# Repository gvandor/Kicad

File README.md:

# Kicad
Theese are my Kicad projects. This is only a hobby.
Projects:
Sidetone: a morse voice generator (for HAM)
Novice: only learning.
Labortap: a power supply for research works

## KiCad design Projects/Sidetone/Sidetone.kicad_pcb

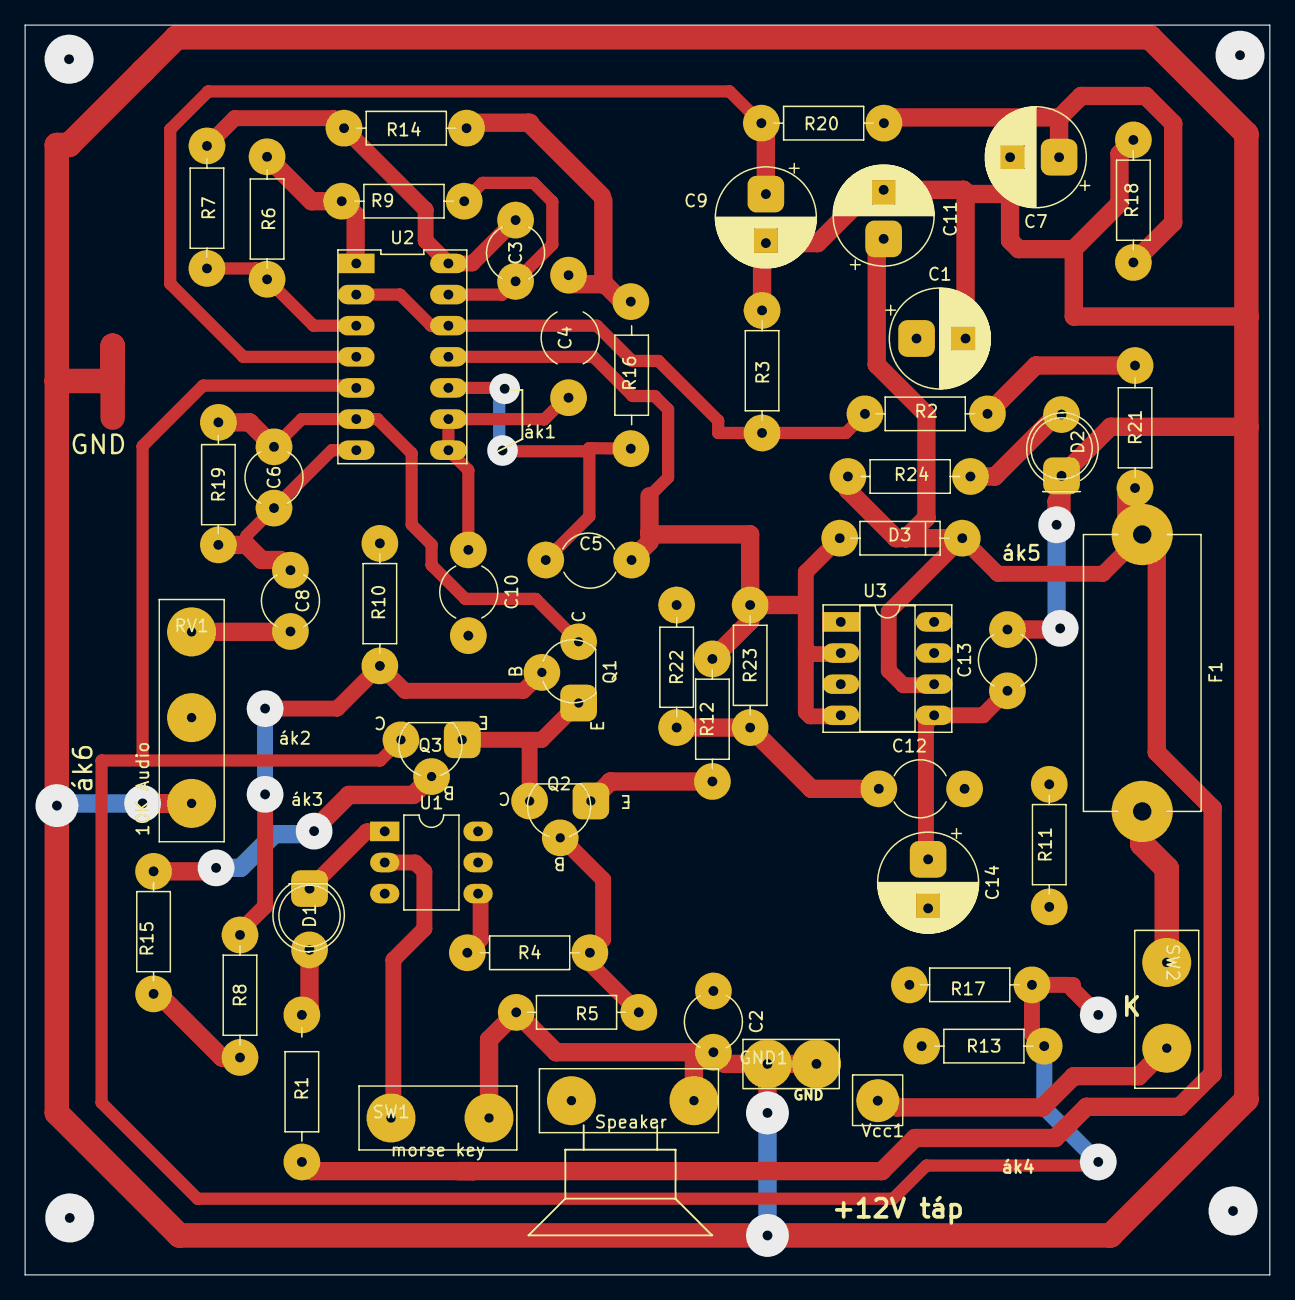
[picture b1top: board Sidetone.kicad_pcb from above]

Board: 2 copper layers, 101.6 x 102.0 mm, 54 parts (0 on the bottom side), 34 nets.

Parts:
4-8ohm1: Speaker; Hangszoro
C1, C7, C9, C11, C14: 100uF/16V; CP_Radial_Elektrolit_D8.0mm_P4.0mm_H12
C2, C4: 20nF; C_Radial_Ceramic_D4.5mm_P5.00mm
C3: 10 nF; C_Radial_Ceramic_D4.5mm_P5.00mm
C5, C6: 10nF; C_Radial_Ceramic_D4.5mm_P5.00mm
C8, C10, C12: 100nF; C_Radial_Ceramic_D4.5mm_P5.00mm
C13: 200nF; C_Radial_Ceramic_D4.5mm_P5.00mm
D1: Red; LED_D5.0mm_P5.0_Clear
D2: Power (Green); LED_D5.0mm_P5.0_Clear
D3: 1N4001; R_Axial_L6.3mm_D2.5mm_P10.0mm_Horizontal
F1: 1A; Fuseholder_22x10mm_Horizontal
GND1: GND
Q1, Q2, Q3: 2N3904; TO-92_Kis_Muanyag_Hazas_Transistor
R1: 750; R_Axial_L6.3mm_D2.5mm_P10.0mm_Horizontal
R2, R3: 10 K; R_Axial_L6.3mm_D2.5mm_P10.0mm_Horizontal
R4, R5: 220 K; R_Axial_L6.3mm_D2.5mm_P10.0mm_Horizontal
R6, R9: 100K; R_Axial_L6.3mm_D2.5mm_P10.0mm_Horizontal
R7: 47K; R_Axial_L6.3mm_D2.5mm_P10.0mm_Horizontal
R8, R15: 330; R_Axial_L6.3mm_D2.5mm_P10.0mm_Horizontal
R10, R17, R18, R19, R20: 10K; R_Axial_L6.3mm_D2.5mm_P10.0mm_Horizontal
R11, R12, R13: 22 K; R_Axial_L6.3mm_D2.5mm_P10.0mm_Horizontal
R14, R16: 33K; R_Axial_L6.3mm_D2.5mm_P10.0mm_Horizontal
R21: 10; R_Axial_L6.3mm_D2.5mm_P10.0mm_Horizontal
R22: 15K; R_Axial_L6.3mm_D2.5mm_P10.0mm_Horizontal
R23, R24: 1K; R_Axial_L6.3mm_D2.5mm_P10.0mm_Horizontal
RV1: 10K Audio; Potenciometer_4Pin_P7mm
SW1: morse key; Morse_Key_Pad_Group_2Pin_P7mm
SW2: On/off; Kapcsolo_Pad_Group_2Pin_P7mm
U1: 4N35; DIP-6_W7.62mm_LongPads
U2: LM324; DIP-14_LM324
U3: LM386; DIP-8_W7.62mm_Socket_LongPads
Vcc1: +Vcc

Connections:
GNDD: 4-8ohm1.2, C1.2, C2.2, C5.2, C7.2, C9.2, C11.2, C13.2, D2.1 (K), D3.2 (A), GND1.1, GND1.2, R3.2, R5.2, R12.2, R18.2, R23.2, RV1.3, SW1.2 (B), U2.11 (V-), U3.2 (-), U3.4 (GND)
unnamed: 4-8ohm1.1, C14.2
unnamed: C3.1, R7.1, R14.1, U2.14
unnamed: C4.2, R14.2, R16.1
unnamed: C7.1, R18.1, R20.2
unnamed: C8.2, RV1.1
unnamed: C10.2, R10.2
unnamed: C12.1, R22.2, R23.1
unnamed: C13.1, C14.1, U3.5
unnamed: D1.2 (A), R1.1
unnamed: D1.1 (K), U1.1
unnamed: D2.2 (A), R24.2
unnamed: C11.1, D3.1 (K), F1.1, R1.2, R21.2, R24.1, U3.6 (V+)
unnamed: Q1.2 (B), R8.2, R10.1
unnamed: C6.1, Q1.3 (C), R11.2, R19.1, U2.6 (-)
unnamed: Q1.1 (E), Q2.3 (C), Q3.1 (E)
unnamed: C2.1, Q2.2 (B), R4.2, R5.1
unnamed: Q2.1 (E), R12.1
unnamed: Q3.2 (B), R15.2
unnamed: Q3.3 (C), R13.2, R17.1, U2.5 (+)
unnamed: R4.1, U1.4
unnamed: R6.1, R9.1, U2.1
unnamed: R8.1, R15.1, R17.2
unnamed: R22.1, RV1.2
unnamed: SW1.1 (A), U1.2
unnamed: F1.2, SW2.1 (A)
unnamed: R6.2, R7.2, U2.3 (+)
unnamed: C1.1, R2.2, R3.1, U2.2 (-), U2.12 (+)
unnamed: C5.1, R16.2, U2.10 (+)
unnamed: C4.1, C10.1, U2.8, U2.9 (-)
unnamed: C3.2, R9.2, U2.13 (-)
unnamed: C6.2, C8.1, C9.1, R2.1, R11.1, R13.1, R19.2, R20.1, R21.1, U1.5, U2.4 (V+), U2.7
unnamed: C12.2, U3.3 (+)
VCC: SW2.2 (B), Vcc1.1

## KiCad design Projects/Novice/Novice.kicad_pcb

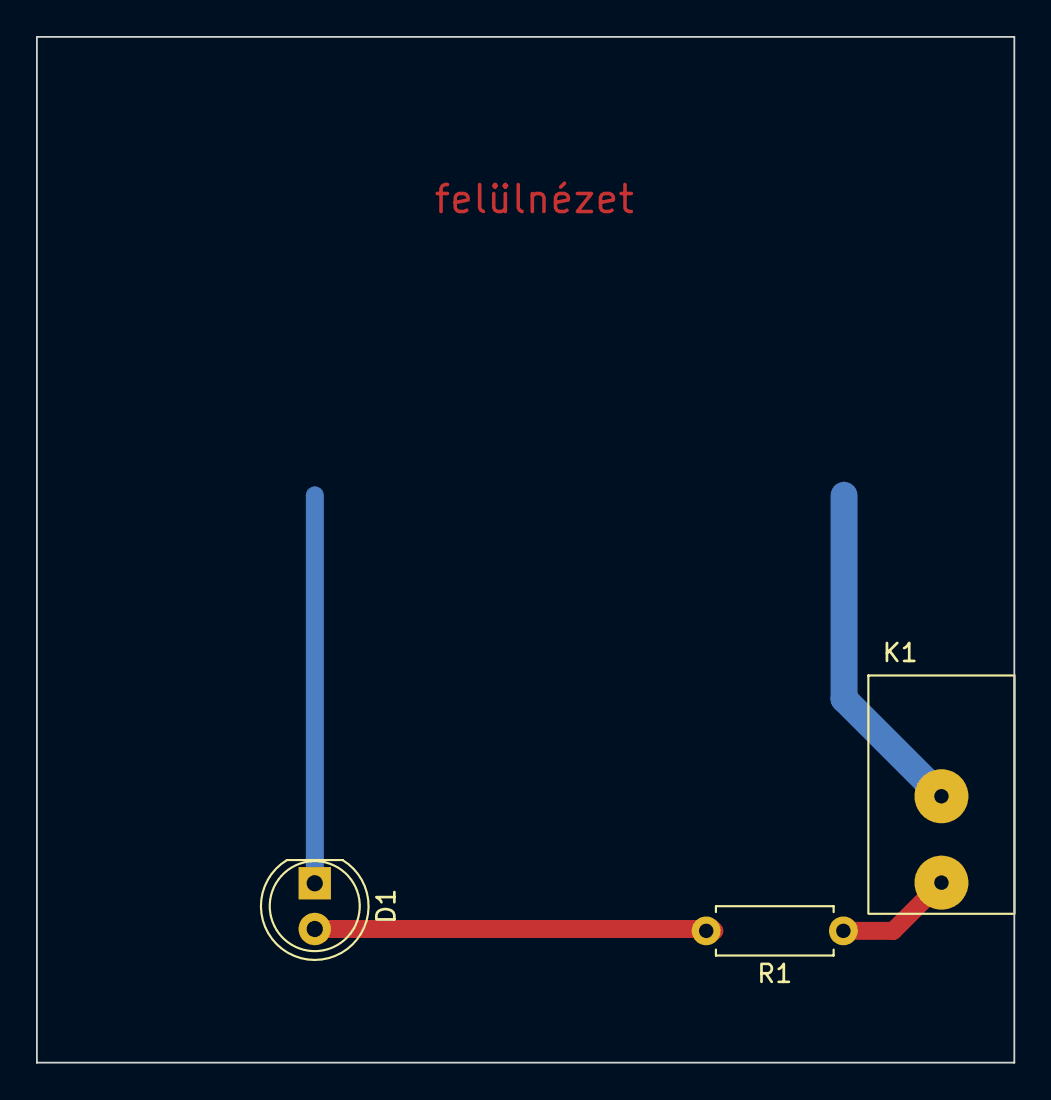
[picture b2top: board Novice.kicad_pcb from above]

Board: 2 copper layers, 54.3 x 57.0 mm, 4 parts (1 on the bottom side), 4 nets.

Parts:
BT1: Battery_Cell; BatteryHolder_Renata_SMTU2032-LF_1x2032
D1: LED; LED_D5.0mm
K1: M2011S3A1W03; kapcsolo
R1: R; R_Axial_DIN0207_L6.3mm_D2.5mm_P7.62mm_Horizontal

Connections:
GND: BT1.2 (-), D1.1 (K)
unnamed: BT1.1 (+), K1.2 (A)
unnamed: D1.2 (A), R1.2
VCC: K1.3 (B), R1.1

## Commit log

2024-02-10 initialing
2024-02-11 20240211
2024-02-13 20240212
2024-02-13 20240213
2024-02-14 20240214
2024-02-15 20240215
2024-02-16 20240216
2024-02-16 20240216-B
2024-02-17 added footprint D Led R
2024-02-17 labnyom szerkesztesek
2024-02-18 modified sidetone schematic
2024-02-18 18-2
2024-02-20 20240220
2024-02-22 20240222
2024-02-22 building pcb 20240222
2024-02-23 20240223
2024-02-24 20240224
2024-02-26 20240226
2024-02-26 20240226 sidetone last update
2024-02-28 20240228
2024-03-02 20240302
2024-05-07 20240507
2024-05-21 20240521
